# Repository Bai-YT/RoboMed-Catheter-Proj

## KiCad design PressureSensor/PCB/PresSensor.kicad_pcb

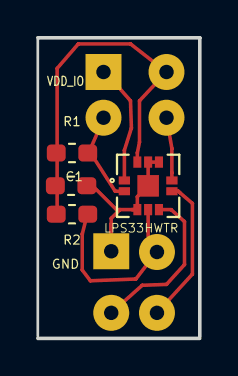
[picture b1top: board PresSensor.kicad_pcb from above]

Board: 2 copper layers, 9.0 x 16.7 mm, 5 parts (0 on the bottom side), 4 nets.

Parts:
C1: C; C_0603_1608Metric_Pad1.05x0.95mm_HandSolder
GND: Conn_01x04; SolderWirePad_2x02_P2.54mm_Drill0.8mm
R1, R2: R; R_0603_1608Metric_Pad1.05x0.95mm_HandSolder
VDD_IO: Conn_01x04; SolderWirePad_2x02_P2.54mm_Drill0.8mm

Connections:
unnamed: C1.1, R1.2, R2.2, VDD_IO.2
unnamed: C1.2, GND.1
unnamed: R1.1, VDD_IO.3
unnamed: GND.2, R2.1

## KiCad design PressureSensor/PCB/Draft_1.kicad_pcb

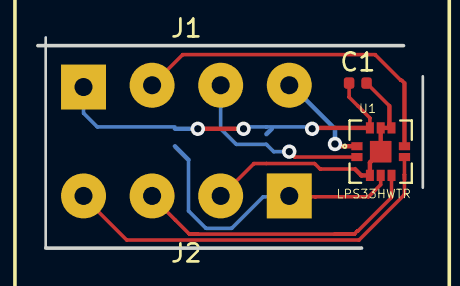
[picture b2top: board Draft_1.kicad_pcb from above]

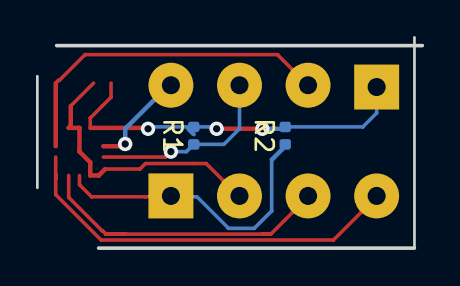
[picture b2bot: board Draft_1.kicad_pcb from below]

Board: 2 copper layers, 21.4 x 11.7 mm, 6 parts (2 on the bottom side), 8 nets.

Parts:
C1: C; C_0402_1005Metric
J1, J2: Conn_01x04; SolderWirePad_1x04_P3.81mm_Drill1mm
R1, R2: R; R_0402_1005Metric
U1: LPS33HWTR; PQFN60P330X330X290-11N

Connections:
unnamed: C1.1, J1.1, R1.2, R2.2, U1.10
unnamed: C1.2, J2.2, U1.3, U1.8, U1.9, U1.EP
unnamed: J1.2, U1.7
unnamed: J1.3, R1.1, U1.2
unnamed: J1.4, U1.1
unnamed: J2.1, R2.1, U1.4
unnamed: J2.3, U1.5
unnamed: J2.4, U1.6

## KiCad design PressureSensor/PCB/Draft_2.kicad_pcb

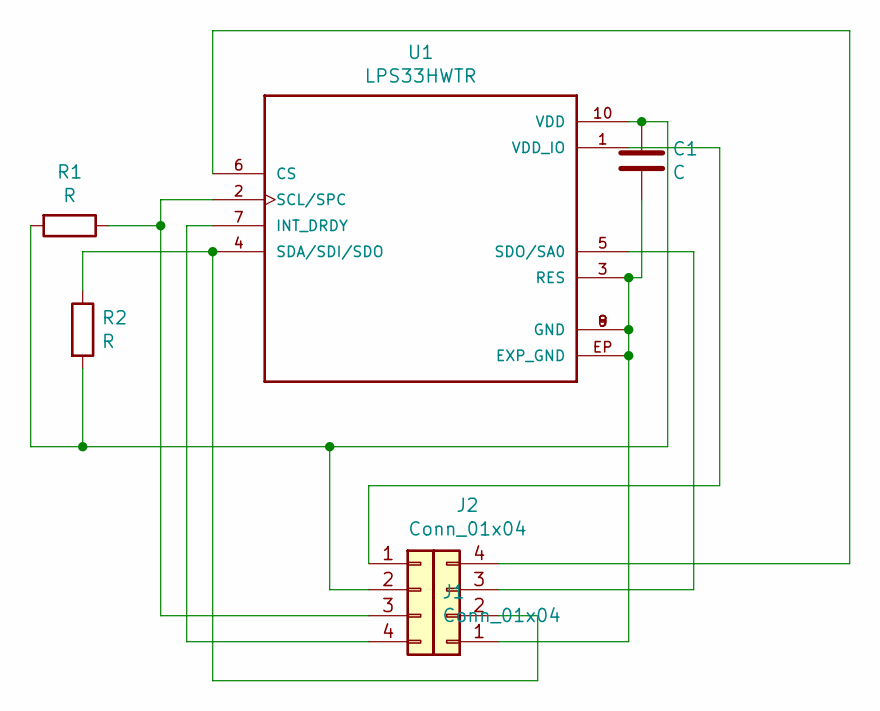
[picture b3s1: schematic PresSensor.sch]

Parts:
C1: C; C_0603_1608Metric_Pad1.05x0.95mm_HandSolder
J1, J2: Conn_01x04; SolderWirePad_2x02_P2.54mm_Drill0.8mm
R1, R2: R; R_0603_1608Metric_Pad1.05x0.95mm_HandSolder
U1: LPS33HWTR; PQFN60P330X330X290-11N

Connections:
unnamed: C1.1, J1.2, R1.2, R2.2, U1.10 (VDD)
unnamed: C1.2, J2.1, U1.3 (RES), U1.8 (GND), U1.9 (GND), U1.EP (EXP_GND)
unnamed: J1.1, U1.1 (VDD_IO)
unnamed: J1.3, R1.1, U1.2 (SCL/SPC)
unnamed: J1.4, U1.7 (INT_DRDY)
unnamed: J2.2, R2.1, U1.4 (SDA/SDI/SDO)
unnamed: J2.3, U1.5 (SDO/SA0)
unnamed: J2.4, U1.6 (CS)

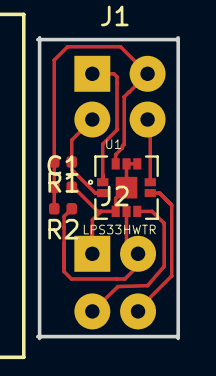
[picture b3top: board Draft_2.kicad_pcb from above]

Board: 2 copper layers, 7.8 x 16.7 mm, 6 parts (0 on the bottom side), 8 nets.
